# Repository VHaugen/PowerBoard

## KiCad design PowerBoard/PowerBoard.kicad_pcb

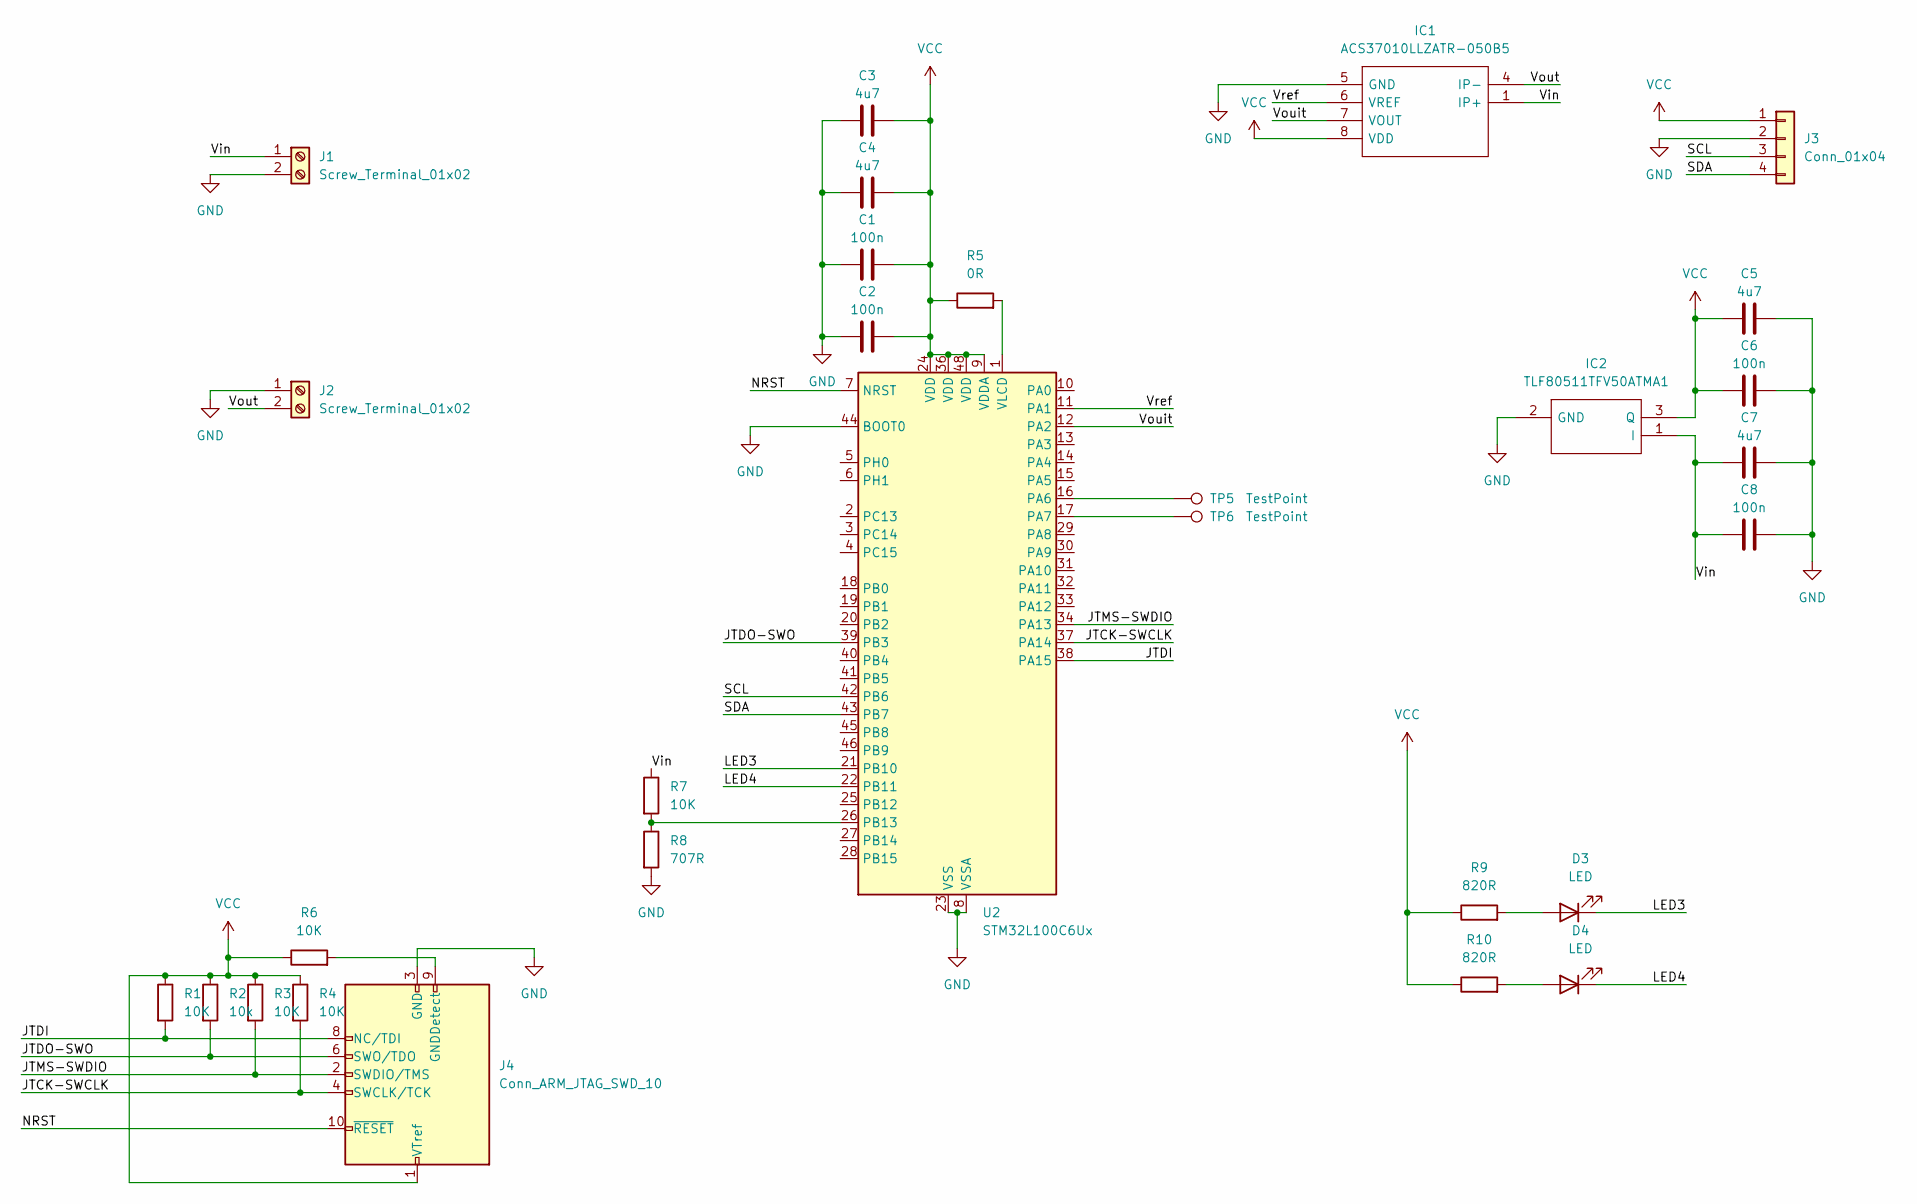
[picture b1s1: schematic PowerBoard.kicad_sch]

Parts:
C1, C2, C6, C8: 100n; C_0805_2012Metric
C3, C4, C5, C7: 4u7; C_0805_2012Metric
D3, D4: LED; LED_0805_2012Metric_Pad1.15x1.40mm_HandSolder
IC1: ACS37010LLZATR-050B5; ACS37010LLZATR050B5; Manufacturer_Part_Number ACS37010LLZATR-050B5
IC2: TLF80511TFV50ATMA1; IDD09E60; Manufacturer_Part_Number TLF80511TFV50ATMA1
J1, J2: Screw_Terminal_01x02; TerminalBlock_RND_205-00001_1x02_P5.00mm_Horizontal
J3: Conn_01x04; PinHeader_1x04_P2.54mm_Vertical
J4: Conn_ARM_JTAG_SWD_10; PinHeader_2x05_P1.27mm_Vertical
R1, R3, R4, R6, R7: 10K; R_0805_2012Metric_Pad1.20x1.40mm_HandSolder
R2: 10k; R_0805_2012Metric_Pad1.20x1.40mm_HandSolder
R5: 0R; R_0201_0603Metric
R8: 707R; R_0805_2012Metric_Pad1.20x1.40mm_HandSolder
R9, R10: 820R; R_0805_2012Metric_Pad1.20x1.40mm_HandSolder
TP5, TP6: TestPoint; TestPoint_Pad_2.0x2.0mm
U2: STM32L100C6Ux; QFN-48-1EP_7x7mm_P0.5mm_EP5.6x5.6mm

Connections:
/JTCK-SWCLK: J4.4 (SWCLK/TCK), R4.2, U2.37 (PA14)
/JTDI: J4.8 (NC/TDI), R1.2, U2.38 (PA15)
/JTDO-SWO: J4.6 (SWO/TDO), R2.2, U2.39 (PB3)
/JTMS-SWDIO: J4.2 (SWDIO/TMS), R3.2, U2.34 (PA13)
/LED3: D3.1 (K), U2.21 (PB10)
/LED4: D4.1 (K), U2.22 (PB11)
/NRST: J4.10 (~RESET), U2.7 (NRST)
/SCL: J3.3, U2.42 (PB6)
/SDA: J3.4, U2.43 (PB7)
/Vin: C7.1, C8.1, IC1.1 (IP+), IC2.1 (I), J1.1, R7.1
/Vouit: IC1.7 (VOUT), U2.12 (PA2)
/Vout: IC1.4 (IP-), J2.2
/Vref: IC1.6 (VREF), U2.11 (PA1)
GND: C1.1, C2.1, C3.1, C4.1, C5.2, C6.2, C7.2, C8.2, IC1.5 (GND), IC2.2 (GND), J1.2, J2.1, J3.2, J4.3 (GND), J4.5 (GND), R8.2, U2.8 (VSSA), U2.23 (VSS), U2.35 (VSS), U2.44 (BOOT0), U2.47 (VSS), U2.49 (VSS)
unnamed: D3.2 (A), R9.2
unnamed: D4.2 (A), R10.2
unnamed: J4.9 (GNDDetect), R6.2
unnamed: TP5.1, U2.16 (PA6)
unnamed: TP6.1, U2.17 (PA7)
unnamed: R7.2, R8.1, U2.26 (PB13)
unnamed: R5.2, U2.1 (VLCD)
VCC: C1.2, C2.2, C3.2, C4.2, C5.1, C6.1, IC1.8 (VDD), IC2.3 (Q), J3.1, J4.1 (VTref), R1.1, R2.1, R3.1, R4.1, R5.1, R6.1, R9.1, R10.1, U2.9 (VDDA), U2.24 (VDD), U2.36 (VDD), U2.48 (VDD)

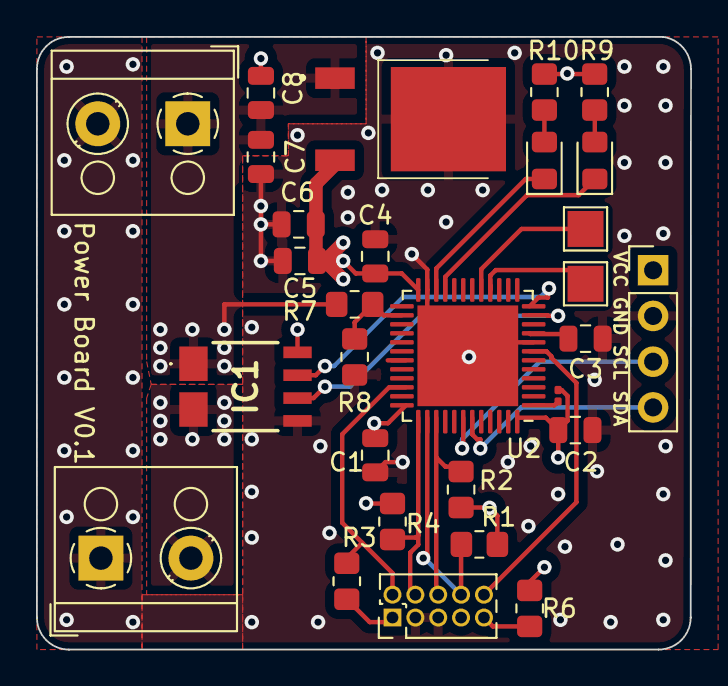
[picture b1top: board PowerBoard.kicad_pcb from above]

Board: 4 copper layers, 36.3 x 34.0 mm, 28 parts (0 on the bottom side), 22 nets.

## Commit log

2024-01-18 need to make it look usable
    Just the init of the project, Code later
2024-01-20 Updated the schematic and removed gerber files from project
2024-01-28 code
    inital setup of stm32 code
